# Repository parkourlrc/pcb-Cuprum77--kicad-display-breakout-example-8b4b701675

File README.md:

# kicad-display Breakout example

This repository contains a simple breakout board for a 1.69" IPS LCD with capacitive touch, and serves as an example of the KiCad project structure.

It was intended to be used with the following display from [AliExpress](https://aliexpress.com/item/1005005238299349.html), however this flat-flex cable is not solderable, and requires a FPC connector to be soldered onto the PCB.
This was originally an oversight on my part, and the PCB that was produced did not feature this footprint, which required manual rework of soldering individual wires directly to the FPC. This version should be fixed, although it has never been produced.

## Requirements

- [KiCad Version 9 or later](https://www.kicad.org/)

## Pulling the repository

Remember to pull recursive submodules to include the display library if you are using git to clone the repository!

```bash
git submodule update --init --recursive
```

## Bill of Materials (BOM)

| Reference | Value | Quantity | Source |
|---|---|---|---|
| DS1 | 1.69" IPS LCD with capacitive touch, FPC connector with 0.5mm pitch | 1 | [Digikey](https://www.digikey.no/en/products/detail/amphenol-cs-fci/SFV18R-4STBE1HLF/4270611) |
| C1, C2, C3 | 100 nF 0603 | 3 | Digikey |
| R1 | 1k 0603 | 1 | Digikey |
| R2 | 10k 0603 | 1 | Digikey |
| R3 | 0R 0603[^1] | 1 | Digikey |
| J1 | 1x12 2.54mm Header | 1 | Digikey |

[^1]: Note that R3 can be shorted by a solder bridge if you don't have a 0R resistor. This is an optional resistor to limit the current to the LCD backlight. The backlight consists of 3 LEDs in parallel and can pull up to 60 mA. 
With a 3V3 supply and a BJT as a switch, the voltage over the LED will be slightly below the nominal forward voltage of 3 V.

## Affiliation

I am in no way affiliated with any of the companies mentioned in this document. The links to the products are provided for convenience and are not endorsements of any kind. The products may be available from other sources, and I encourage you to shop around for the best price and availability.

The PCB however were paid for by Aisler as a part of a single-time sponsorship through a store-credit. I am under no contract or obligation to promote their services, and I have no financial interest in their success.

## License

This project is licensed under CERN Open Hardware License Version 2 - Strong Reciprocity (CERN-OHL-S-2.0). See [LICENSE](LICENSE) for more details.

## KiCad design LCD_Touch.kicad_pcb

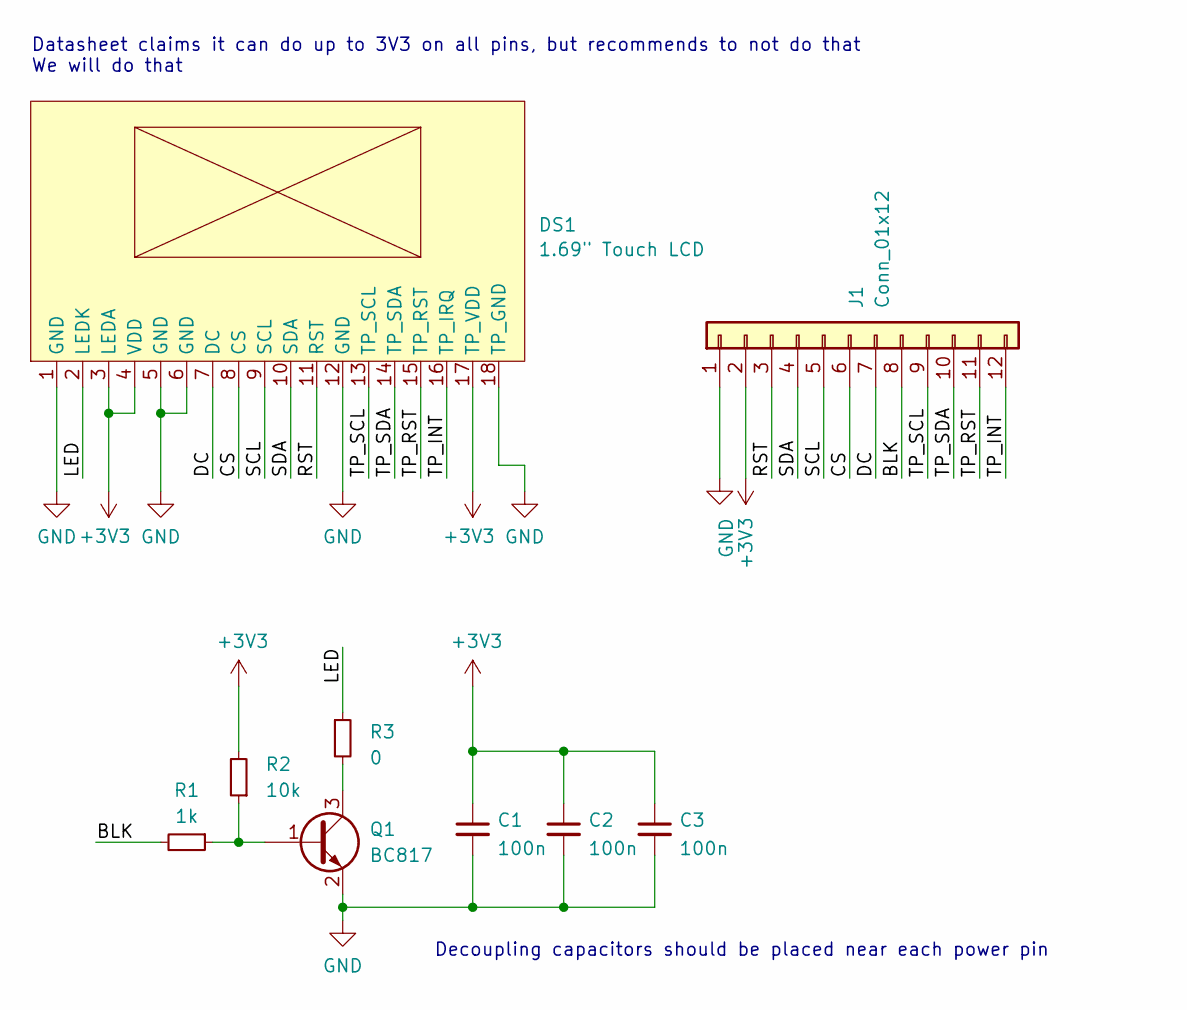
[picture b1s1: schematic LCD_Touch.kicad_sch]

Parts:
C1, C2, C3: 100n; C_0603_1608Metric
DS1: 1.69" Touch LCD; AMPHENOL_SFV18R-4STBE1HLF
J1: Conn_01x12; PinHeader_1x12_P2.54mm_Vertical
Q1: BC817; SOT-23
R1: 1k; R_0603_1608Metric
R2: 10k; R_0603_1608Metric
R3: 0; R_0603_1608Metric

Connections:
+3V3: C1.1, C2.1, C3.1, DS1.3 (LEDA), DS1.4 (VDD), DS1.17 (TP_VDD), J1.2, R2.2
/BLK: J1.8, R1.2
/CS: DS1.8 (CS), J1.6
/DC: DS1.7 (DC), J1.7
/LED: DS1.2 (LEDK), R3.1
/RST: DS1.11 (RST), J1.3
/SCL: DS1.9 (SCL), J1.5
/SDA: DS1.10 (SDA), J1.4
/TP_INT: DS1.16 (TP_IRQ), J1.12
/TP_RST: DS1.15 (TP_RST), J1.11
/TP_SCL: DS1.13 (TP_SCL), J1.9
/TP_SDA: DS1.14 (TP_SDA), J1.10
GND: C1.2, C2.2, C3.2, DS1.1 (GND), DS1.5 (GND), DS1.6 (GND), DS1.12 (GND), DS1.18 (TP_GND), DS1.S1 (GND), DS1.S2 (GND), J1.1, Q1.2 (E)
unnamed: Q1.1 (B), R1.1, R2.1
unnamed: Q1.3 (C), R3.2

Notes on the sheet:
Decoupling capacitors should be placed near each power pin
Datasheet claims it can do up to 3V3 on all pins, but recommends to not do that We will do that

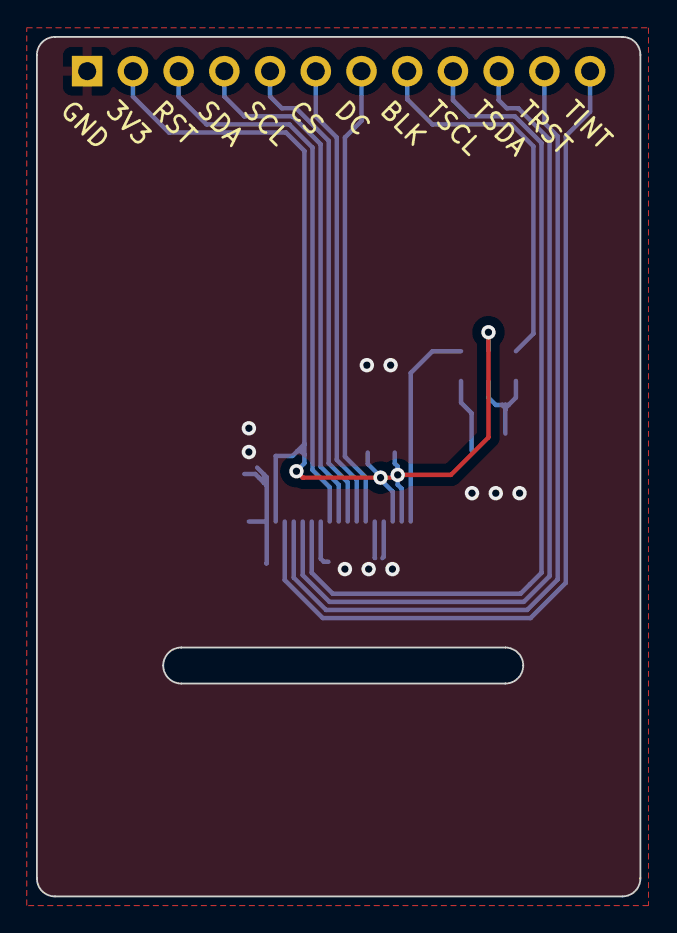
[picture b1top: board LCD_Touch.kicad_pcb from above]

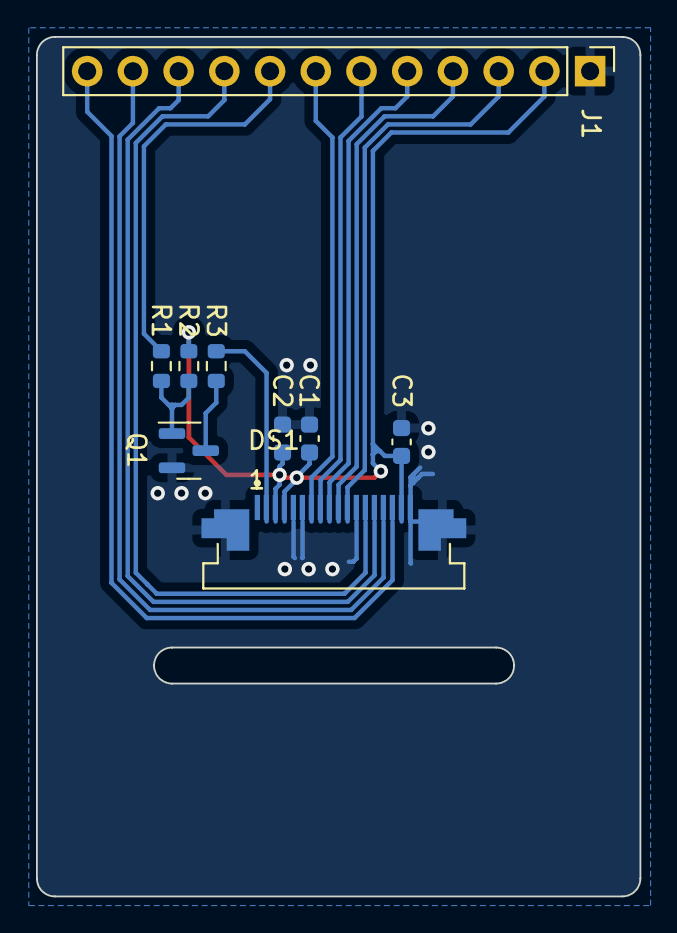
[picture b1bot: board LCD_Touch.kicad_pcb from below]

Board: 2 copper layers, 33.5 x 47.8 mm, 9 parts (9 on the bottom side), 15 nets.
